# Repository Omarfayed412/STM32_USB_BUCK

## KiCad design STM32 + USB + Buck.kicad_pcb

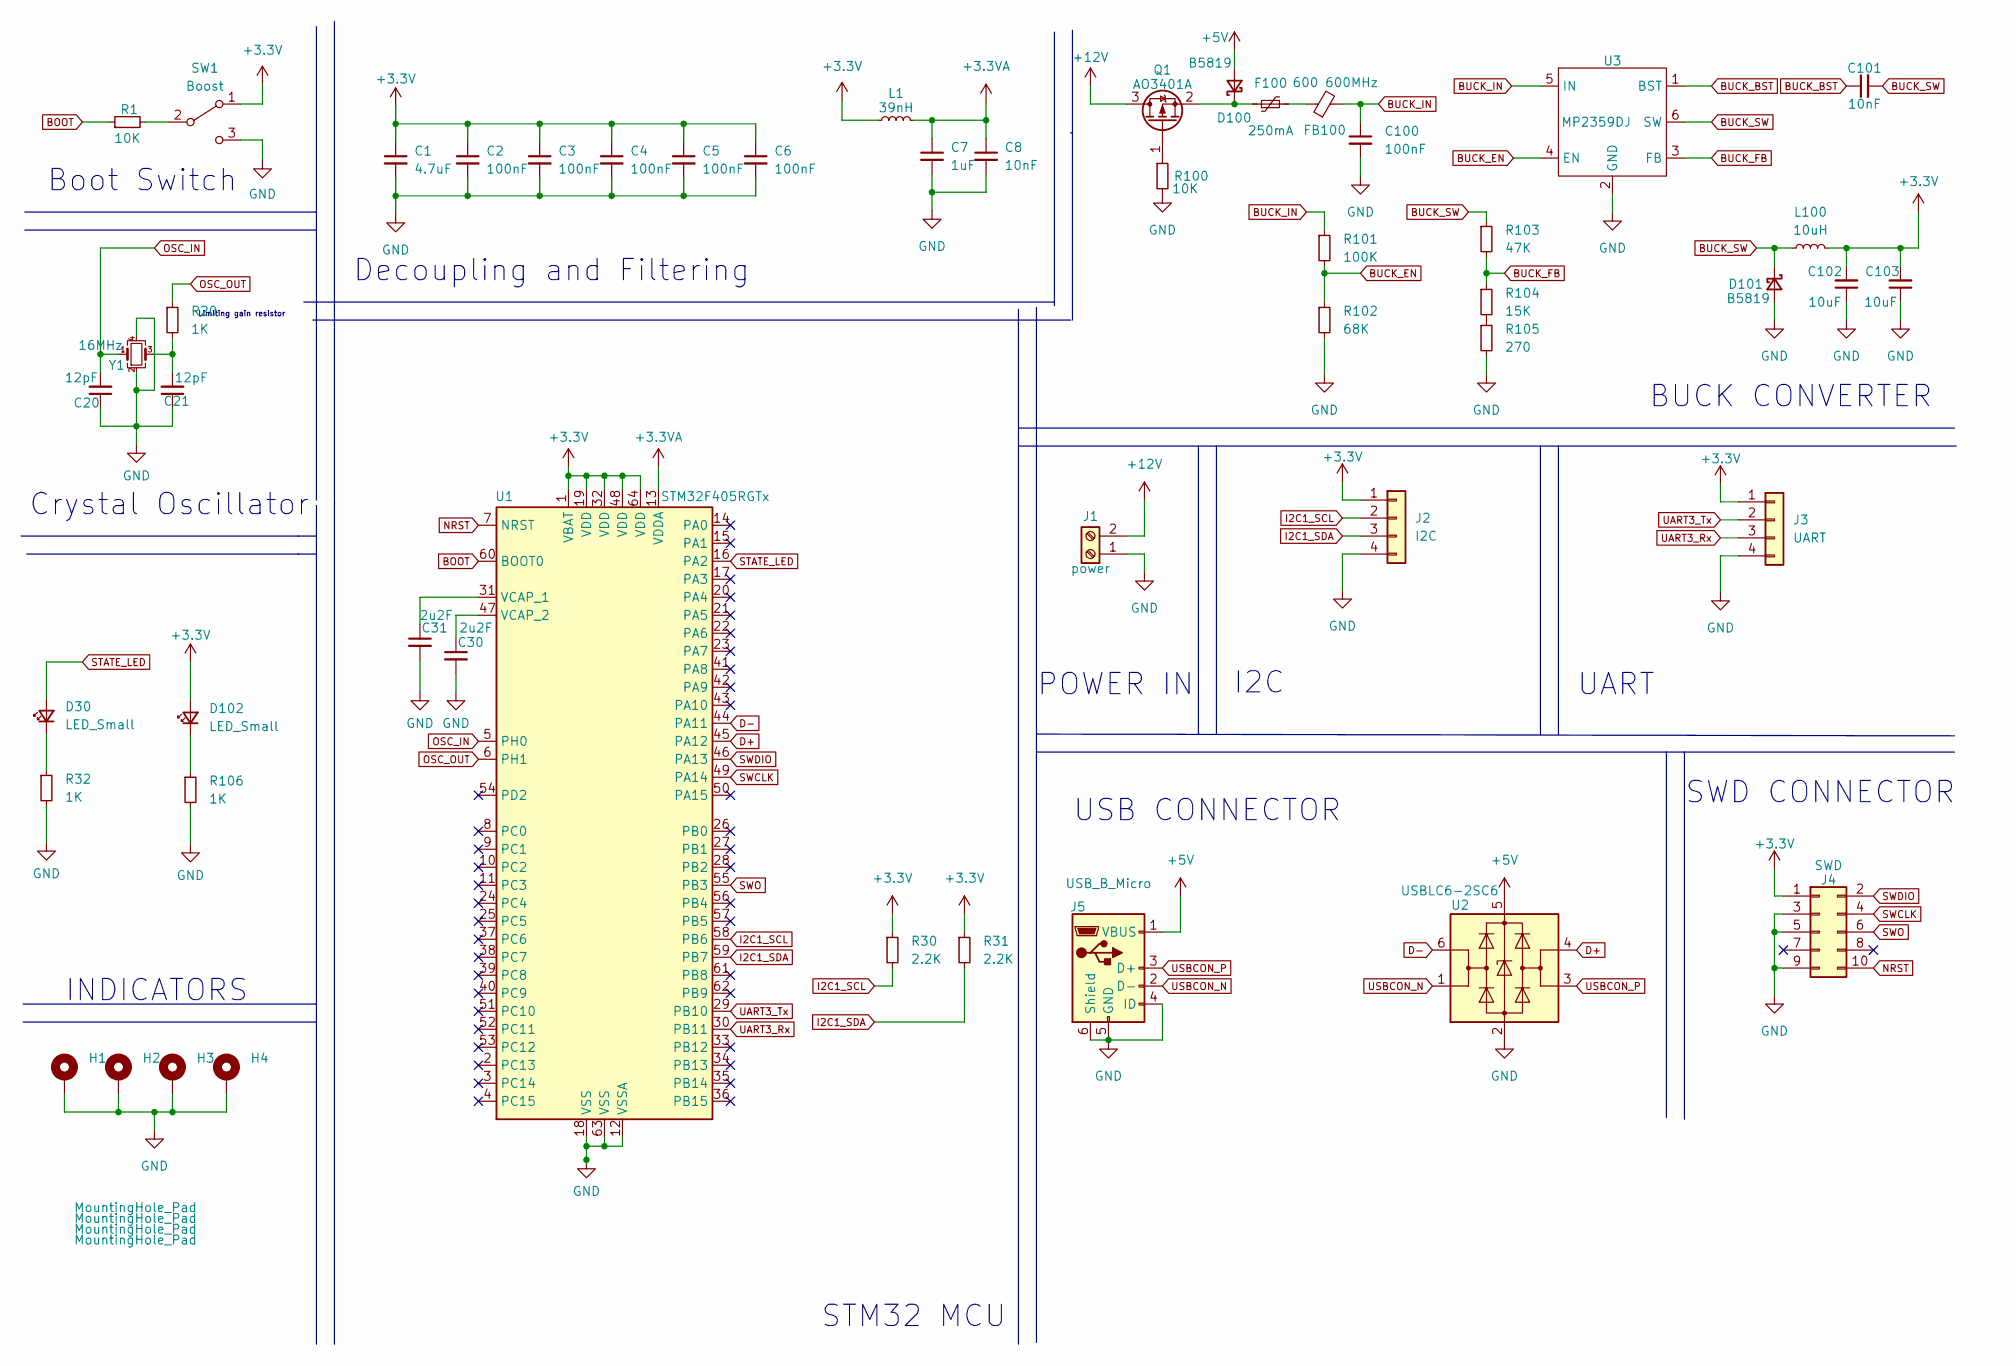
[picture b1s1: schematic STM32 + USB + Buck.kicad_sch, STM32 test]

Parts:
C1: 4.7uF; C_0603_1608Metric
C2, C3, C4, C5, C6: 100nF; C_0402_1005Metric
C7: 1uF; C_0402_1005Metric
C8: 10nF; C_0402_1005Metric
C20, C21: 12pF; C_0603_1608Metric
C30, C31: 2u2F; C_0201_0603Metric
C100: 100nF; C_0603_1608Metric
C101: 10nF; C_0201_0603Metric
C102, C103: 10uF; C_0603_1608Metric
D30, D102: LED_Small; LED_0603_1608Metric
D100: B5819; D_0603_1608Metric
D101: B5819; D_0805_2012Metric
F100: 250mA; Fuse_0603_1608Metric
FB100: 600 600MHz; L_0805_2012Metric
H1, H2, H3, H4: MountingHole_Pad; MountingHole_4.3mm_M4_Pad_Via
J1: power; TerminalBlock_Phoenix_MKDS-1,5-2_1x02_P5.00mm_Horizontal
J2: I2C; JST_PH_S4B-PH-K_1x04_P2.00mm_Horizontal
J3: UART; JST_PH_S4B-PH-K_1x04_P2.00mm_Horizontal
J4: SWD; PinSocket_2x05_P1.27mm_Vertical_SMD
J5: USB_B_Micro; USB_Micro-B_Molex_47346-0001
L1: 39nH; L_0402_1005Metric
L100: 10uH; L_Abracon_ASPI-4030S
Q1: AO3401A; SOT-23
R1, R100: 10K; R_0603_1608Metric
R20, R32, R106: 1K; R_0603_1608Metric
R30, R31: 2.2K; R_0402_1005Metric
R101: 100K; R_0201_0603Metric
R102: 68K; R_0201_0603Metric
R103: 47K; R_0201_0603Metric
R104: 15K; R_0201_0603Metric
R105: 270; R_0201_0603Metric
SW1: Boost; SW_SPDT_PCM12
U1: STM32F405RGTx; LQFP-64_10x10mm_P0.5mm
U2: USBLC6-2SC6; SOT-23-6
U3: MP2359DJ; SOT-23-6
Y1: 16MHz; Crystal_SMD_3225-4Pin_3.2x2.5mm

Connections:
+3.3V: C1.1, C2.1, C3.1, C4.1, C5.1, C6.1, C102.2, C103.2, D102.2 (A), J2.1, J3.1, J4.1, L1.1, L100.2, R30.1, R31.1, SW1.1 (A), U1.1 (VBAT), U1.19 (VDD), U1.32 (VDD), U1.48 (VDD), U1.64 (VDD)
+3.3VA: C7.1, C8.1, L1.2, U1.13 (VDDA)
+5V: D100.2 (A), J5.1 (VBUS), U2.5 (VBUS)
+12V: J1.2, Q1.3 (D)
BOOT: R1.1, U1.60 (BOOT0)
BUCK_BST: C101.1, U3.1 (BST)
BUCK_EN: R101.2, R102.1, U3.4 (EN)
BUCK_FB: R103.2, R104.1, U3.3 (FB)
BUCK_IN: C100.1, FB100.2, R101.1, U3.5 (IN)
BUCK_SW: C101.2, D101.1 (K), L100.1, R103.1, U3.6 (SW)
D+: U1.45 (PA12), U2.4 (I/O2)
D-: U1.44 (PA11), U2.6 (I/O1)
GND: C1.2, C2.2, C3.2, C4.2, C5.2, C6.2, C7.2, C8.2, C20.1, C21.1, C30.2, C31.2, C100.2, C102.1, C103.1, D101.2 (A), H1.1, H2.1, H3.1, H4.1, J1.1, J2.4, J3.4, J4.3, J4.5, J4.9, J5.4 (ID), J5.5 (GND), J5.6 (Shield), R32.2, R100.2, R102.2, R105.2, R106.2, SW1.3 (C), U1.12 (VSSA), U1.18 (VSS), U1.63 (VSS), U2.2 (GND), U3.2 (GND), Y1.2, Y1.4
I2C1_SCL: J2.2, R30.2, U1.58 (PB6)
I2C1_SDA: J2.3, R31.2, U1.59 (PB7)
NRST: J4.10, U1.7 (NRST)
unnamed: C21.2, R20.2, Y1.3
unnamed: C30.1, U1.47 (VCAP_2)
unnamed: C31.1, U1.31 (VCAP_1)
unnamed: D30.1 (K), R32.1
unnamed: D100.1 (K), F100.1, Q1.2 (S)
unnamed: D102.1 (K), R106.1
unnamed: F100.2, FB100.1
unnamed: Q1.1 (G), R100.1
unnamed: R1.2, SW1.2 (B)
unnamed: R104.2, R105.1
OSC_IN: C20.2, U1.5 (PH0), Y1.1
OSC_OUT: R20.1, U1.6 (PH1)
STATE_LED: D30.2 (A), U1.16 (PA2)
SWCLK: J4.4, U1.49 (PA14)
SWDIO: J4.2, U1.46 (PA13)
SWO: J4.6, U1.55 (PB3)
UART3_Rx: J3.3, U1.30 (PB11)
UART3_Tx: J3.2, U1.29 (PB10)
USBCON_N: J5.2 (D-), U2.1 (I/O1)
USBCON_P: J5.3 (D+), U2.3 (I/O2)

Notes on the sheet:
Boot Switch
I2C
Crystal Oscillator
INDICATORS
UART
Limiting gain resistor
USB CONNECTOR
STM32 MCU
SWD CONNECTOR
Decoupling and Filtering
BUCK CONVERTER
POWER IN

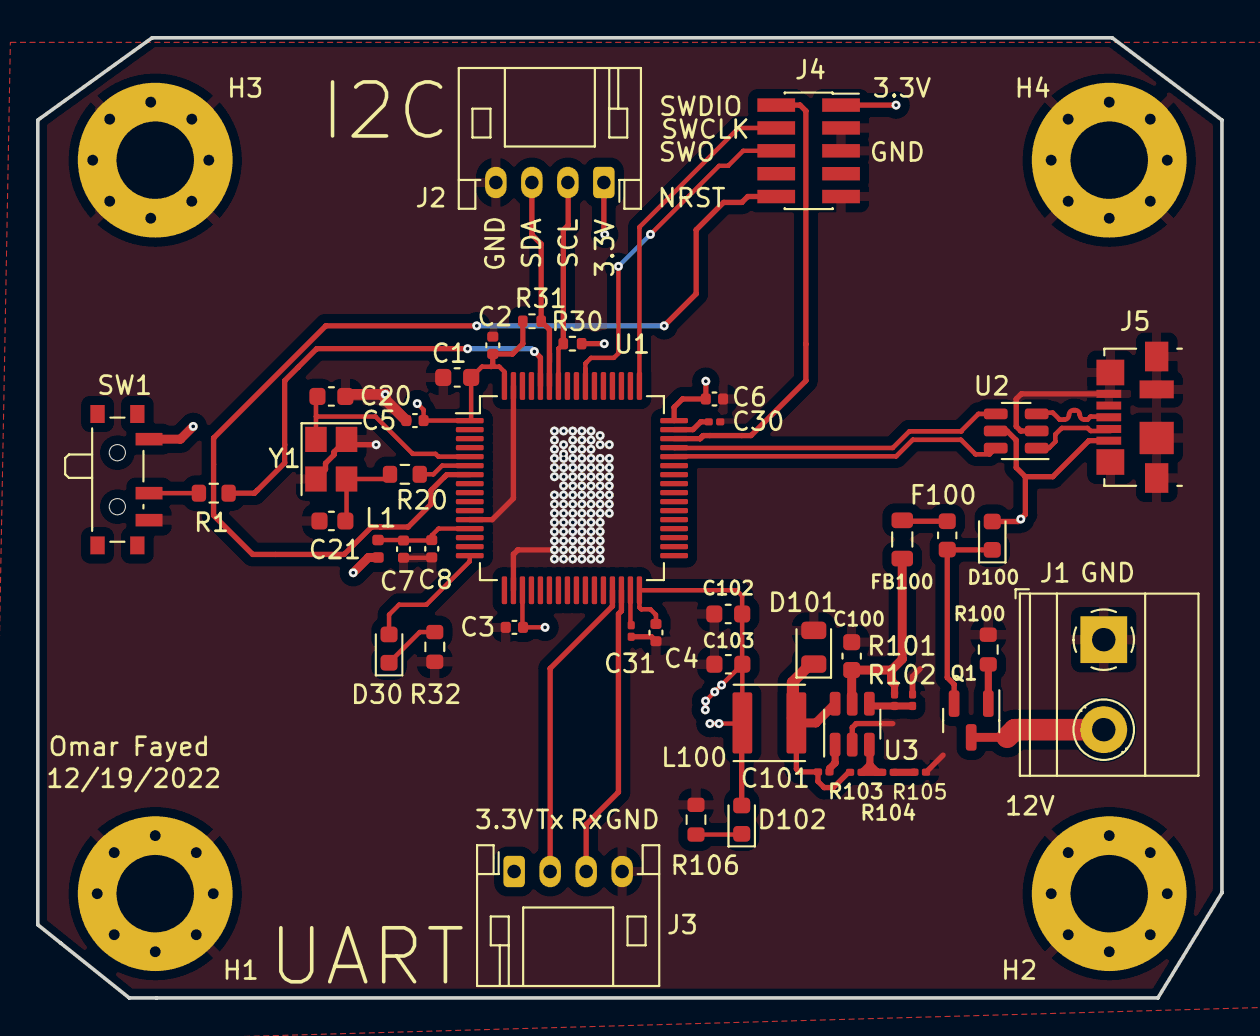
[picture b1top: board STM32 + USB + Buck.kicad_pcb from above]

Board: 4 copper layers, 65.8 x 53.3 mm, 51 parts (0 on the bottom side), 36 nets.

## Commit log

2023-11-23 Added gthe PCB files for Kicad
